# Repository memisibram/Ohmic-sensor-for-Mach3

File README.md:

# Ohmic-sensor-for-Mach3
Touch ohmic sensor for Mach3 plasma cutters

### About the project
This project is designed for use in plasma cutters using a Mach3 control card that communicates via a USB port.

While performing a probe search with the torch, the pilot arc cable is disabled and the torch nozzle is connected to an opamp integrated circuit. Once the probe search is complete, the pilot arc cable is reconnected, allowing the ohmic sensor to be used in HF-initiated pilot arc plasma cutters.

Project video.
 - Video: [https://youtu.be/aqT4PSTSzog](https://youtu.be/aqT4PSTSzog)

### Pictures

### License GNU GPL v3.0

### Donation

  -  Paypal: memisibram@gmail.com or https://www.paypal.me/memisibram

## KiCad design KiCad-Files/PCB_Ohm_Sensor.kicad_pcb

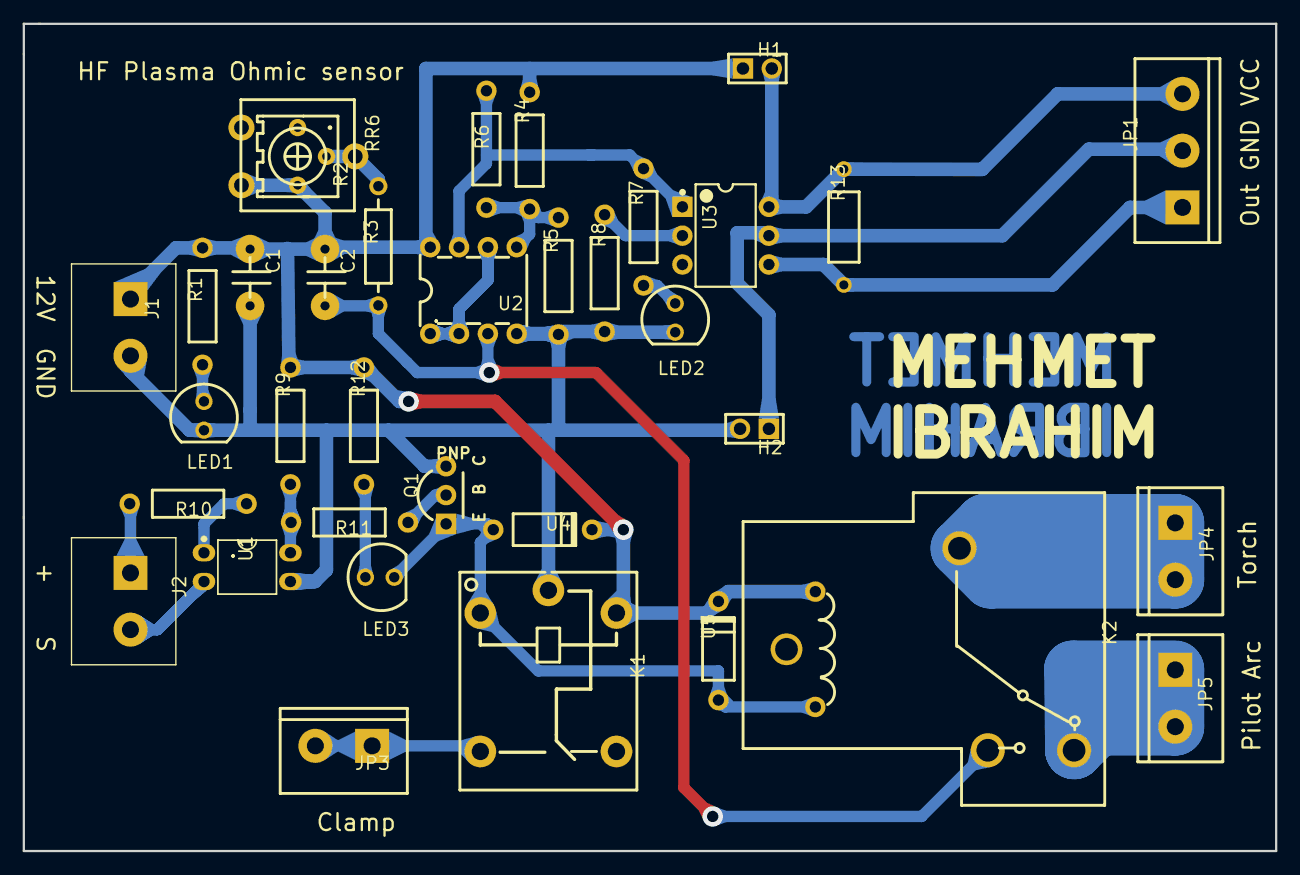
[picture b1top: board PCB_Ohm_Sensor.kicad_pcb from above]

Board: 2 copper layers, 110.4 x 72.9 mm, 35 parts (0 on the bottom side), 23 nets.

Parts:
C1: 100NF; CERAMIC CAPACITOR 100NF
C2: 47NF; CERAMIC CAPACITOR 100NF
H1, H2: Header-Male-2.54_1x2; HDR-TH_2P-P2.54-V-M-1
J1, J2: REF; TERMINALBLOCK_ONSHORE_1X02_P5.00MM_HORIZONTAL
JP1: M03; SCREWTERMINAL-5MM-3
JP3, JP4, JP5: M025MM; SCREWTERMINAL-5MM-2
K1: SRD-12VDC-SL-C; RELAY-TH_SRD-XXVDC-XL-C
K2: RELAY 12V S; RELAY-TH_SLA-12VDC-SL-C
LED1: Pwr; LED-TH_BD5.0-P2.54-FD_C9900023552
LED2: Out; LED-TH_BD5.0-P2.54-FD_C9900023552
LED3: LED_5MM; LED-TH_BD5.0-P2.54-FD_C9900023552
Q1: SS8550; TO-92-3_L4.8-W3.7-P2.54-L
R1, R7, R12: 470Ω; RES-TH_BD2.4-L6.3-P10.30-D0.6
R2: 2MΩ; RES-ADJ-TH_3362P
R3: 1MΩ; RES-TH_BD2.2-L6.5-P10.50-D0.6
R4: 15K; RES-TH_BD2.4-L6.3-P10.30-D0.6
R5: 100K; RES-TH_BD2.4-L6.3-P10.30-D0.6
R6: 470KΩ; RES-TH_BD2.4-L6.3-P10.30-D0.6
R8: 300Ω; RES-TH_BD2.4-L6.3-P10.30-D0.6
R9: 10K; RES-TH_BD2.4-L6.3-P10.30-D0.6
R10: 2kΩ; RES-TH_BD2.4-L6.3-P10.30-D0.6
R11: 1K; RES-TH_BD2.4-L6.3-P10.30-D0.6
R13: 10kΩ; RES-TH_BD2.7-L6.2-P10.20-D0.4
RR6: ACP; ACP SPAIN
U1: PC817B; DIP-4_L4.6-W6.5-P2.54-LS7.6-BL
U2: LM358N; PDIP-8_L10.2-W5.9-P2.54-LS7.6-BL
U3: H11L2M; DIP-6_L8.5-W6.4-P2.54-LS7.6-BL
U4, U5: 1N4007; DO-41_BD2.4-L4.7-P8.70-D0.6-RD

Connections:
GND: C1.2, H2.2, J1.2, K1.5, LED1.2, LED2.2, Q1.3, R5.2, R8.2, U1.3, U2.4
J2_1: J2.1, R10.1
JP4_1: JP4.1, JP4.2, K2.5
JP5_1: JP5.1, JP5.2, K2.1
K1_2: JP3.1, JP3.2, K1.2
LED3_2: K1.1, K2.3, LED3.2, Q1.1, U4.2, U5.2
R1_2: LED1.1, R1.2
R2_2: R2.2, R3.1, RR6.3
R7_2: LED2.1, R7.2
R8_1: R8.1, U3.2
R11_2: Q1.2, R11.2
R12_2: LED3.1, R12.2
U1_1: R10.2, U1.1
U1_2: J2.2, U1.2
U1_4: R9.2, R11.1, U1.4
U2_3: C2.2, K2.2, R3.2, U2.3
U2_5: R4.2, R5.1, R6.2, U2.5
U2_6: U2.1, U2.2, U2.6
U2_7: R6.1, R7.1, U2.7, U3.1
U3_4: JP1.1, R13.2, U3.4
U3_5: H2.1, JP1.2, U3.5
U3_6: H1.2, JP1.3, R13.1, U3.6
VCC: C1.1, C2.1, H1.1, J1.1, K1.4, K2.4, R1.1, R2.3, R4.1, R9.1, R12.1, RR6.2, U2.8, U4.1, U5.1
